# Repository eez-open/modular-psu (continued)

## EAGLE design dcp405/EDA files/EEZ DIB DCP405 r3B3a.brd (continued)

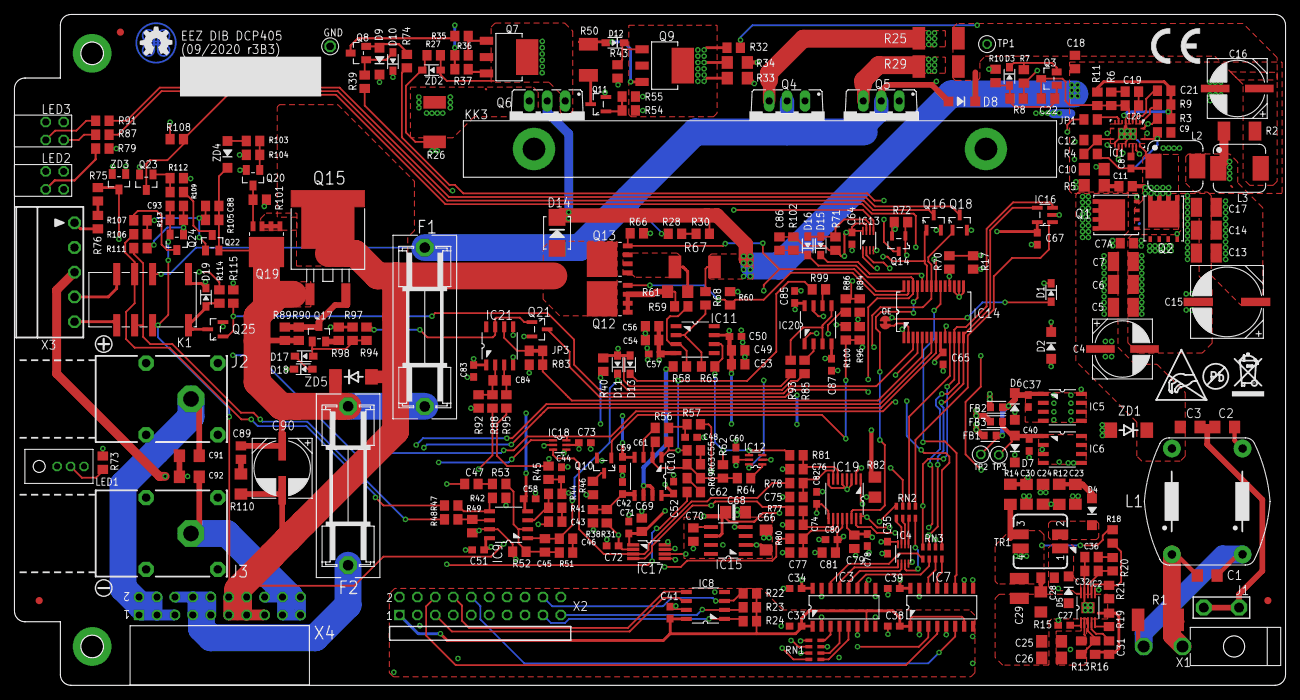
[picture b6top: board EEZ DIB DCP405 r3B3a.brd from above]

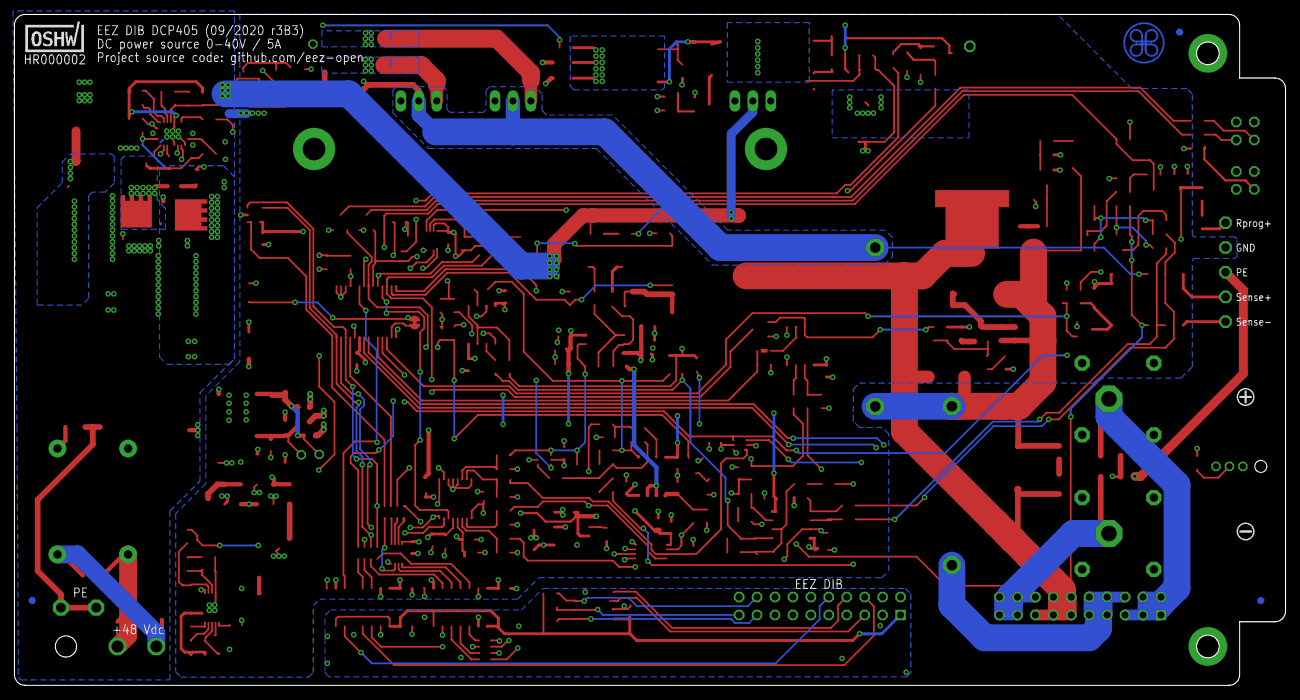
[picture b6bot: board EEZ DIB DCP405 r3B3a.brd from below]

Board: 4 copper layers, 180.0 x 95.0 mm, 322 parts (2 on the bottom side), 199 nets.

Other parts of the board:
EEZ_SIGNATURE: SIGNATURESMALL; SIGNATURE_5MM
U$1: RECYCLE_BIN1/8
U$2: CE_5MM
U$6: ESD_SYMBOL
U$7: PB_SMALL

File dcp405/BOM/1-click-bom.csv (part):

References,Qty,Description,Manufacturer,MPN,Manufacturer,MPN,Manufacturer,MPN,Manufacturer,MPN,Digikey,Mouser,RS,Newark,Farnell
"C1, C2, C3, C91, C92",5,10n/200V,,885342207005,,311-4491-1-ND,,CC1206KRX7RABB103,,VJ1206Y103KXCTW1BC,,,,,
"C10, C25, C26",3,2u2,,1276-2723-1-ND,,UMK316B7225KLHT,,CL31B225KBHNNNE,,,,,,,
C11,1,1n,,VJ0805A102JXACW1BC,,732-7858-1-ND,,GRM2195C1H102JA01D,,CL21C102JBCNNNC,,,,,
C12,1,15p,,MC0805N150J101CT,,1276-1163-1-ND,,C0805C150J5GACTU,,CL21C150JBANNNC,,,,,
"C13, C14, C17",3,10u,,GRT31CR61H106KE01L,,1276-6736-1-ND,,UMK316BBJ106KL-T,,CL31A106KBHNNNE,,,,,
C15,1,EEEFK1J101P,,EEEFK1J101P,,PCE3819CT-ND,,EEEFK1J101P,,EEEFK1J101P,,,,,
"C18, C53, C56, C69, C70, C79, C81",7,1u,,VJ0805Y105KXXTW1BC,,587-1283-1-ND,,C0805C105K4RACTU,,CL21B105KOFNNNE,,,,,
"C19, C21, C31, C36, C49, C54, C88, C93",8,10n,,VJ0805Y103JXXPW1BC,,490-7194-1-ND,,08055C103KAT2A,,CC0805KRX7R9103,,,,,
C20,1,150p,,0805N151J500CT,,1276-1828-1-ND,,C0805C151J5GACTU,,CC0805JRNPO9BN151,,,,,
C22,1,470p,,MC0805N471J500CT,,732-7837-1-ND,,0805CG471J9BB,,CC0805JRNPO9BN471,,,,,
"C23, C24, C30, C66",4,4u7,,C3216X7R1E475K160AC,,1276-2970-1-ND,,C1206C475K3RACTU,,GCM31CR71E475KA55L,,,,,
C28,1,330p,,C0805C331J5GACTU,,1276-1189-1-ND,,0805N331J500CT,,CL21C331JBANNNC,,,,,
C29,1,22u,,MC1210X226K250CT,,1276-3373-1-ND,,CL32A226KAJNNNE,,CL32A226KAJNNNE,,,,,
"C32, C45, C61",3,33p,,MC0805N330J500CT,,1276-1105-1-ND,,C0805C330J5GACTU,,CL21C330JBANNNC,,,,,
"C4, C16",2,EEEFK1H470P,,EEEFK1H470P,,PCE3815CT-ND,,EEEFK1H470P,,EEEFK1H470P,,,,,
"C43, C47",2,100p,,C0805C101JAGACTU,,399-15000-1-ND,,CC0805JRNP09BN101,,CL21C101JBANNNC,,,,,
"C5, C6, C7",3,4u7/100V,,CGA6M3X7S2A475K200AB,,587-5034-1-ND,,-,,,,,,,
"C55, C74, C75, C76, C77, C84, C86",7,4n7,,GRM2165C1H472JA01D,,732-12255-1-ND,,C2012C0G1H472J060AA,,GRM2165C1H472JA01D,,,,,
C62,1,6n8,,MC0805B682K500CT,,1276-1799-1-ND,,GRM2195C1H682JA01D,,CL21B682KBANNNC,,,,,
C68,1,4u7 tant.,,T491A475K006AT,,399-9717-1-ND,,T491A475K006AT,,T491A475K006AT,,,,,
"C7A, C9, C89",3,470n,,MC0805F474Z500CT,,1276-6482-1-ND,,0805CG471J9BB,,CL21B474KBFNNNE,,,,,
"C8, C27, C33, C34, C35, C37, C38, C39, C40, C41, C42, C44, C48, C50, C51, C52, C57, C58, C59, C60, C64, C65, C67, C71, C72, C73, C78, C80, C82, C83, C85, C87",32,100n,,C0603C104K4RAC7081,,490-4774-1-ND,,VJ0603Y104KXJAT,,CL10B104KA8NNNC,,,,,
C90,1,HHXC630A330MHA0,,-,,-,,,,,,,,,
"D1, D3, D10, D11, D12, D13, D15, D17, D18, D19",10,BAS316,,"BAS316,115",,1727-7370-1-ND,,"BAS316,115",,"BAS316,115",,,,,
D14,1,SK55,,SBRT5A50SA-13,,SK56A-LTPMSCT-ND,,SK56B R4,,SK55-DIO,,,,,
"D2, D4, D5",3,SKL16,,RB160MM-60TR,,RB160MM-60CT-ND,,RB160MM-60TR,,SKL16-DIO,,,,,
"D6, D7, D9",3,SKL14,,PMEG4010EGWX,,1727-7335-1-ND,,PMEG4010EGWX,,SKL14-DIO,,,,,
"F1, F2",2,ZH32,,-,,ZH32,,,,,,,,,
"FB1, FB2, FB3",3,BLM18AG102SH1D,,BLM18AG102SN1D,,490-7809-1-ND,,BLM18AG102SH1D,,BLM18AG102SH1D,,,,,
IC1,1,LM5145RGYT,,LM5145RGYT,,296-47121-1-ND,,-,,,,,,,
IC11,1,LTC2050HVCS8#PBF,,LTC2050HVCS8#PBF-ND,,LTC2050HVCS8#PBF,,-,,,,,,,
"IC12, IC18",2,SN74LVC1G3157DCKR,,SN74LVC1G3157DCKR,,296-14909-1-ND,,SN74LVC1G3157DCKR,,SN74LVC1G3157DCKR,,,,,
IC13,1,74AUP1G74DC.125,,"74AUP1G74DC,125",,1727-6029-1-ND,,"74AUP1G74DC,125",,74AUP1G74DC.125,,,,,
IC14,1,MCP23S17-E/SS,,MCP23S17-E/SS,,MCP23S17-E/SS-ND,,MCP23S17-E/SS,,MCP23S17-E/SS,,,,,
IC15,1,REF5025AIDR,,REF5025AIDG4,,296-39165-1-ND,,REF5025AID,,-,,,,,
IC16,1,TC77-5.0MCTTR,,TC77-5.0MCTTRCT-ND,,TC77-5.0MCTTR,,TC77-5.0MCTTR,,,,,,,
IC17,1,DAC8552IDGKR,,296-46082-1-ND,,-,,,,,,,,,
IC19,1,ADS1120IPWR,,296-37280-1-ND,,-,,,,,,,,,
IC2,1,TPS54060DGQ,,TPS54060DGQ .,,296-37148-1-ND,,TPS54060DGQ,,-,,,,,
IC20,1,LM293D,,LM293DT,,296-12848-1-ND,,LM293ADR,,LM293D-ST,,,,,
IC21,1,MAX9141ESA,,MAX9141ESA+,,MAX9141ESA+-ND,,MAX9141ESA+,,-,,,,,
"IC3, IC7",2,SI8641BB-B-IS1,,SI8641BB-B-IS1,,336-2566-ND,,Si8641BB-B-IS1,,-,,,,,
IC4,1,SN74LVC1G139DCUR,,SN74LVC1G139DCUR,,296-18203-1-ND,,-,,,,,,,
IC5,1,MC78L05,,MC78L05ABDR2G,,MC78L05ACDR2GOSCT-ND,,MC78L05ACDG,,MC78L05ACDG,,,,,
IC6,1,MC79L05,,MC79L05ACDR2G,,MC79L05ABDGOS-ND,,MC79L05ACDR2G,,MC79L05ACDG,,,,,
IC8,1,M24C32-WMN6P,,M24C32-WMN6P,,497-8644-1-ND,,M24C32-WMN6P,,M24C32-WMN6P,,,,,
"IC9, IC10",2,TL072D,,TL072CDT,,296-1282-1-ND,,TL072CD,,TL072CD-ST,,,,,
J1,1,4907,,36-4907-ND,,61-1537-11/0031,,,,,,,,,
J2,1,FCR7350R or BSM-420-R,,FCR7350R,,-,,SWEB 8094 Au / RT,,BSM-420-R,,,,,
J3,1,FCR7350B or BSM-420-B,,FCR7350B,,-,,SWEB 8094 Au / SW,,BSM-420-B,,,,,
K1,1,FTR-C1GA005G-B05,,-,,FTR-C1GA005G,,FTR-C1GA005G-B05,,,,,,,
L1,1,RN112-4-02-0M7,,817-2100-ND,,-,,,,,,,,,
L2,1,ETQ-P4M100KFM,,ETQP4M100KFM,,P124167CT-ND,,,,,,,,,
L3,1,HPI0630-3R3,,IHLP2020CZER3R3M11,,445-180834-1-ND,,HPI0630-3R3,,,,,,,
LED1,1,WP42WUM/EGW,,754-1718-ND,,L-42WUM/1EGWT,,,,,,,,,
LED2,1,WP934MD/2LID,,754-2000-ND,,-,,,,,,,,,
LED3,1,WP934MD/LYLID,,754-2008-ND,,-,,,,,,,,,
Q1,1,BSC117N08NS5ATMA1,,BSC117N08NS5ATMA1,,BSC117N08NS5ATMA1CT-ND,,BSC117N08NS5ATMA1,,,,,,,
"Q10, Q16, Q18, Q21, Q25",5,2N7002,,2N7002K-7,,T2N7002AKLMCT-ND,,2N7002,,2N7002LT1G,,,,,
Q11,1,BSS205NH6327XTSA1,,BSS205NH6327XTSA1,,BSS205NH6327XTSA1CT-ND,,BSS205NH6327XTSA1,,BSS205NH6327XTSA1,,,,,
"Q12, Q13",2,PSMN0R9-25YLC,,"PSMN0R9-25YLC,115",,1727-5292-1-ND,,"PSMN0R9-25YLC,115",,PSMN0R9-25YLC.115,,,,,
Q14,1,BSS84P,,BSS84PH6327XTSA2,,BSS84PH6433XTMA1CT-ND,,BSS84P,,,,,,,
Q15,1,BT139B-600E,,"BT139B-600,118",,1740-1053-1-ND,,"BT139B-600,118",,BT139B-600E.118,,,,,
Q17,1,FMMT493TA,,FMMT493ATA,,FMMT493CT-ND,,FMMT493TA,,FMMT493TA,,,,,
Q19,1,PSMN013-60YL,,PSMN013-60YLX,,1727-2589-1-ND,,-,,,,,,,
Q2,1,BSC039N06NSATMA1,,BSC039N06NSATMA1,,BSC039N06NSATMA1CT-ND,,BSC039N06NSATMA1,,BSC039N06NS,,,,,
"Q20, Q23, Q24",3,MMBT5551,,MMBT5551LT1G,,MMBT5551LT1GOSCT-ND,,MMBT5551LT1G,,MMBT5551,,,,,
"Q3, Q8, Q22",3,MMBT5401,,MMBT5401LT3G,,MMBT5401-FDICT-ND,,MMBT5401,,MMBT5401,,,,,
"Q4, Q5",2,D45H11FP,,497-12486-5-ND,,-,,,,,,,,,
Q6,1,FQPF11P06,,FQPF11P06FS-ND,,FQPF11P06,,-,,,,,,,
Q7,1,BCP56,,BCP56TX,,BCP5616QTADICT-ND,,BCP56-16T3G,,BCP56-16T1G,,,,,
Q9,1,NZT605,,NZT605,,NZT605CT-ND,,NZT605,,NZT605,,,,,
R10,1,11K,,MCWR08X1102FTL,,A126334CT-ND,,CRCW080511K0FKEA,,0805S8F1102T5E,,,,,
"R106, R111",2,750R,,MCWR08X7500FTL,,A126385CT-ND,,RN73C2A750RB,,0805S8F7500T5E,,,,,
R107,1,3K3,,MCWR08X3301FTL,,A129755CT-ND,,CRG0805F3K3,,0805S8F3301T5E,,,,,
R11,1,3K9,,MCWR08X3901FTL,,A126369CT-ND,,CRCW08053K90FKEA,,SMD0805-3K9-1%,,,,,
"R16, R32, R40, R45, R56, R57, R74, R77, R78, R80, R81",11,2K2,,RC0805FR-072K2L,,311-2.20KCRCT-ND,,CRCW08052K20FKEA,,0805S8F2201T5E,,,,,
"R18, R20",2,86K6,,ERJ6ENF8662V,,311-86.6KCRCT-ND,,CRCW080586K6FKTABC,,,,,,,
R19,1,330K,,MCWR08X3303FTL,,A126361CT-ND,,CRCW0805330KFKEA,,0805S8F3303T5E,,,,,
"R2, R50",2,15R/0.75W,,CRGCQ2010J15R,,A129910CT-ND,,RK73HW2HTTE15R0F,,201007J0150T4E,,,,,
"R21, R63",2,8K2,,MCWR08X8201FTL,,311-8.20KCRCT-ND,,CRG0805F8K2,,0805S8J0822T5E,,,,,
"R25, R29",2,0R1/2-3W,,MCLRP12JTWSR100,,696-1680-1-ND,,CRA2512-FZ-R100ELF,,LRP12FTDRR100,,,,,
R26,1,2R2/2-3W,,35202R2JT,,CRM2512-JW-2R2ELFCT-ND,,35222R2JT,,WF25P2R2JTL,,,,,
"R27, R28, R30, R35, R84, R86, R96, R100, R102",9,4K7,,CRGCQ0805F4K7,,311-4.70KCRCT-ND,,CRG0805F4K7,,0805S8F4701T5E,,,,,
"R3, R6, R7, R17, R22, R23, R24, R31, R41, R44, R52, R53, R71, R83, R85, R92, R93, R95, R99, R108, R109",21,10K,,RC0805FR-0710KL,,311-10.0KCRCT-ND,,CRG0805F10K,,RC0805FR-0710K,,,,,
"R36, R43, R69, R70, R89, R90, R94, R101",8,1K,,WCR0805-1K0FI,,RC0805FR-071KL,,CRG0805F1K0,,RC0805FR-071K,,,,,
"R37, R38, R54",3,220R,,WCR0805-220RFI,,RMCF0805FT220RCT-ND,,CRG0805F220R,,0805S8F2200T5E,,,,,
"R39, R46, R62, R103, R104",5,22K,,MCWR08X2202FTL,,RMCF0805FT22K0CT-ND,,CRCW080522K0FKEA,,0805S8J0223T5E,,,,,
"R4, R64, R75, R76, R79, R114",6,470R,,WCR0805-470RFI,,311-470CRCT-ND,,CRG0805F470R,,RC0805FR-07470R,,,,,
"R42, R49",2,7K5 0.1%,,MCTC0525B7501T5E,,YAG1974CT-ND,,AR05BTCW7501,,,,,,,
"R47, R48",2,124K 0.1%,,WF08U1243BTL,,P124KDACT-ND,,CPF0805B124KE1,,ERA6AEB1243V,,,,,
"R5, R12, R14, R15, R33, R34, R82",7,10R,,RC1206FR-0710RL,,311-10.0CRCT-ND,,CR1206-FX-10R0ELF,,1206S4J0100T5E,,,,,
"R58, R65",2,39K 0.1%,,MCWF08R3902BTL,,P20774CT-ND,,CPF-A-0805B39KE1,,AR05BTCW3902,,,,,
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
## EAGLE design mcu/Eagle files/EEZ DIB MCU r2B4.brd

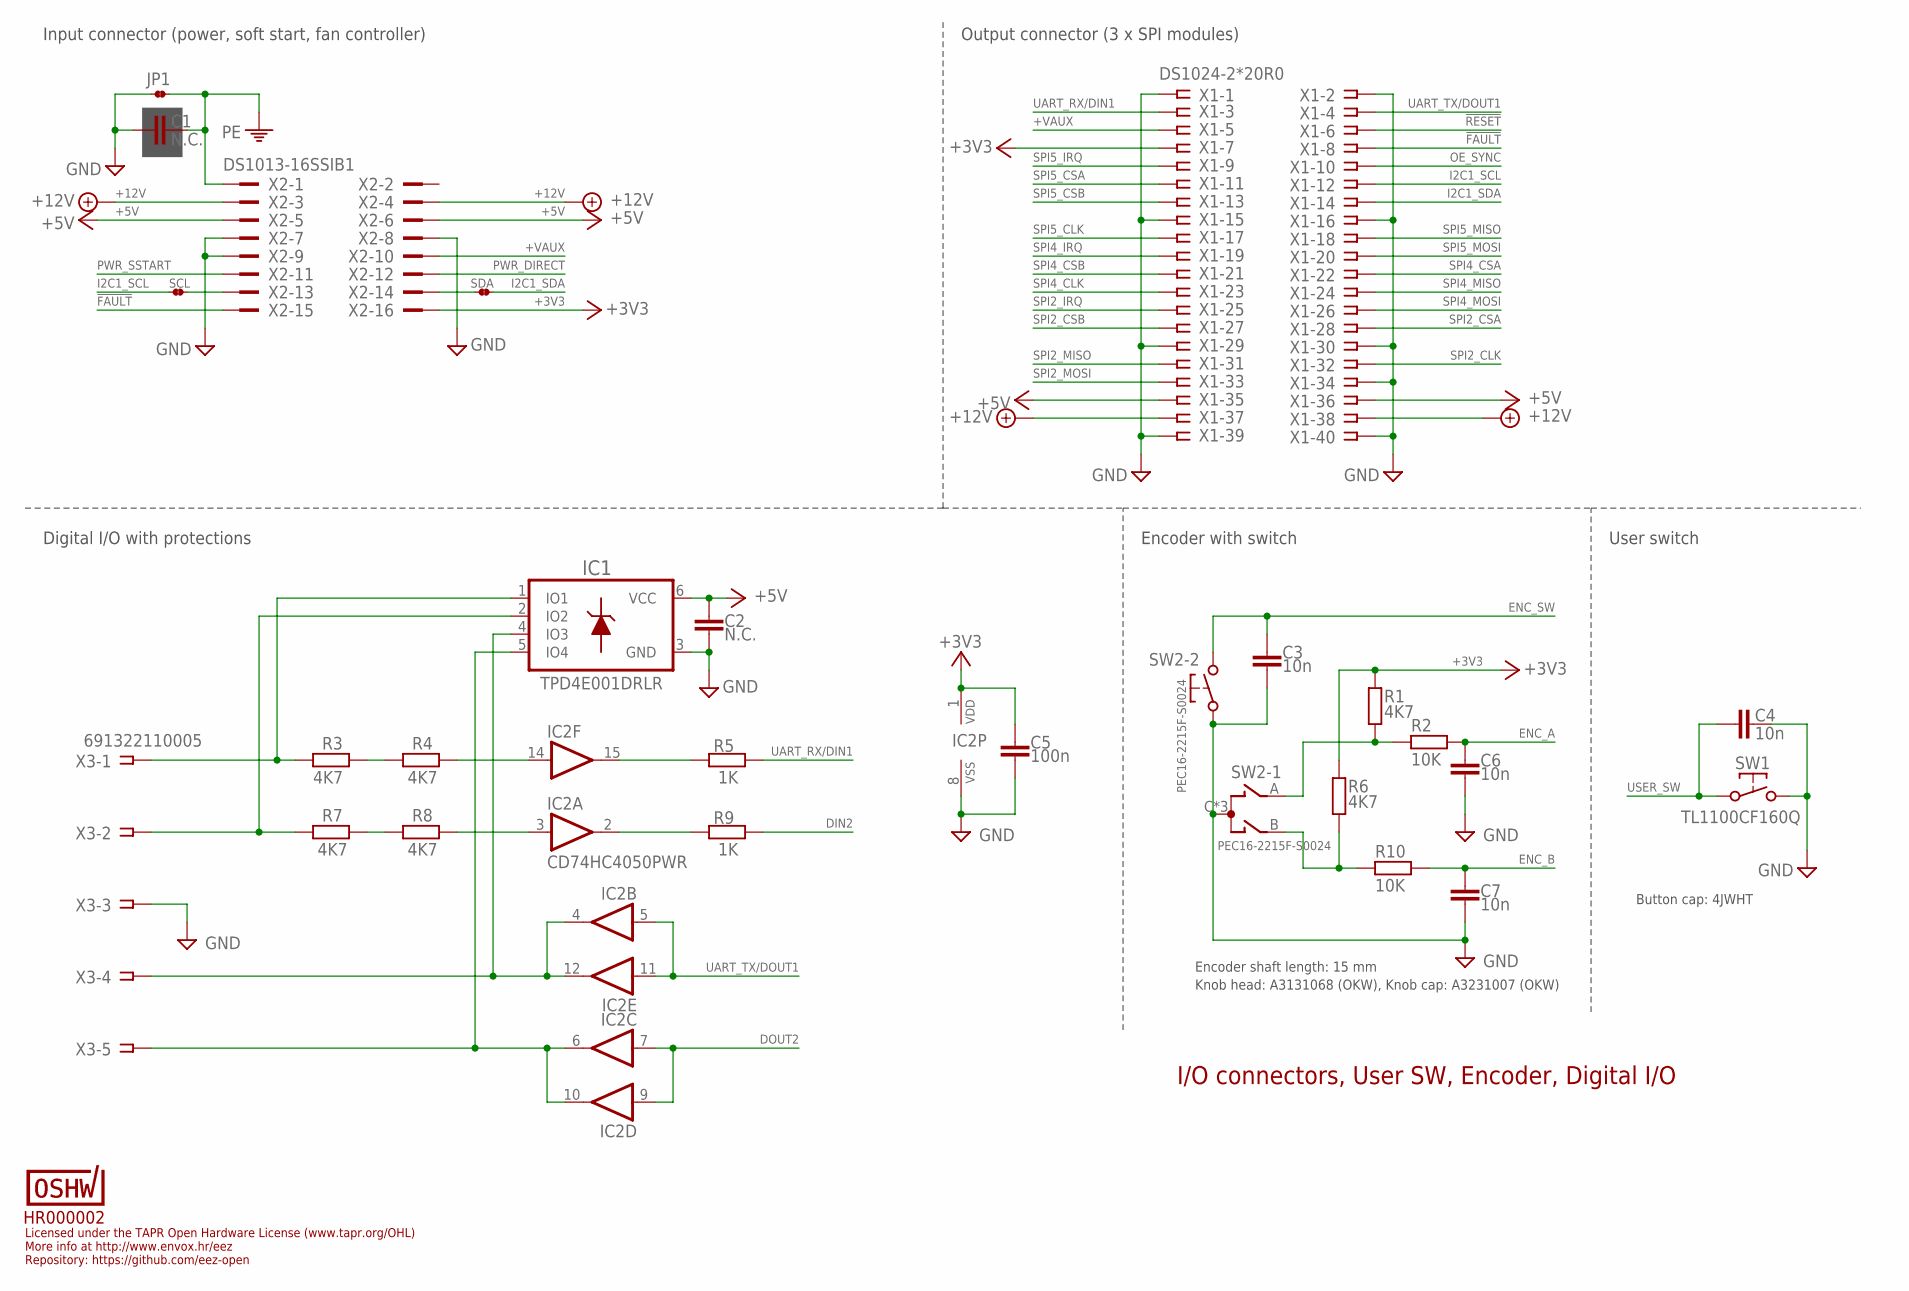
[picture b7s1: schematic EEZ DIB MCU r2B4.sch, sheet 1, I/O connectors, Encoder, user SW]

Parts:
C1: N.C.; C0805
C2: N.C.; C0603
C3, C4, C6, C7: 10n; C0805
C5: 100n; C0603
IC1: TPD4E001DRLR; DRL6
IC2: CD74HC4050PWR; PW16
JP1: JP2-NOCUT
R1, R3, R4, R6, R7, R8: 4K7; R0805
R2, R10: 10K; R0805
R5, R9: 1K; R0805
SCL: JP2-NOCUT
SDA: JP2-NOCUT
SW1: TL1100CF160Q; TL1100C
SW2: PEC16-2215F-S0024; PEC16-2215F
U$3: HR000002; CERT-SMALL-SILK
X1: DS1024-2*20R0; ZL263-40DG
X2: DS1013-16SSIB1; IDC-16PIN
X3: 691322110005; MC1,5/5-G-3,5

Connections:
!FAULT: X1.8, X2.15; also elsewhere on the board
!RESET: X1.6; also elsewhere on the board
+3V3: C5.1, IC2.1 (VDD), R1.1, R6.1, X1.7, X2.16; also elsewhere on the board
+5V: C2.1, IC1.6 (VCC), X1.35, X1.36, X2.5, X2.6; also elsewhere on the board
+12V: X1.37, X1.38, X2.3, X2.4
+VAUX: X1.5, X2.10; also elsewhere on the board
DIN2: R9.2; also elsewhere on the board
DOUT2: IC2.7 (I), IC2.9 (I); also elsewhere on the board
ENC_A: C6.2, R2.1; also elsewhere on the board
ENC_B: C7.1, R10.1; also elsewhere on the board
ENC_SW: C3.2, SW2.E (2); also elsewhere on the board
EOUT_A: R6.2, R10.2, SW2.B
EOUT_B: R1.2, R2.2, SW2.A
GND: C1.2, C2.2, C3.1, C4.1, C5.2, C6.1, C7.2, IC1.3 (GND), IC2.8 (VSS), JP1.1, SW1.2, SW2.C, SW2.D (1), SW2.GND1 (C), SW2.GND2 (C), X1.1, X1.2, X1.15, X1.16, X1.29, X1.30, X1.34, X1.39, X1.40, X2.7, X2.8, X2.9, X3.3; also elsewhere on the board
I2C1_SCL: SCL.1, X1.12; also elsewhere on the board
I2C1_SDA: SDA.2, X1.14; also elsewhere on the board
unnamed: IC1.1 (IO1), R3.1, X3.1
unnamed: SCL.2, X2.13
unnamed: SDA.1, X2.14
unnamed: IC1.2 (IO2), R7.1, X3.2
unnamed: R7.2, R8.1
unnamed: R3.2, R4.1
unnamed: IC2.15 (O), R5.1
unnamed: IC2.2 (O), R9.1
unnamed: IC2.14 (I), R4.2
unnamed: IC2.3 (I), R8.2
unnamed: IC1.4 (IO3), IC2.4 (O), IC2.12 (O), X3.4
unnamed: IC1.5 (IO4), IC2.6 (O), IC2.10 (O), X3.5
OE_SYNC: X1.10; also elsewhere on the board
PE: C1.1, JP1.2, X2.1; also elsewhere on the board
PWR_DIRECT: X2.12; also elsewhere on the board
PWR_SSTART: X2.11; also elsewhere on the board
SPI2_CLK: X1.32; also elsewhere on the board
SPI2_CSA: X1.28; also elsewhere on the board
SPI2_CSB: X1.27; also elsewhere on the board
SPI2_IRQ: X1.25; also elsewhere on the board
SPI2_MISO: X1.31; also elsewhere on the board
SPI2_MOSI: X1.33; also elsewhere on the board
SPI4_CLK: X1.23; also elsewhere on the board
SPI4_CSA: X1.22; also elsewhere on the board
SPI4_CSB: X1.21; also elsewhere on the board
SPI4_IRQ: X1.19; also elsewhere on the board
SPI4_MISO: X1.24; also elsewhere on the board
SPI4_MOSI: X1.26; also elsewhere on the board
SPI5_CLK: X1.17; also elsewhere on the board
SPI5_CSA: X1.11; also elsewhere on the board
SPI5_CSB: X1.13; also elsewhere on the board
SPI5_IRQ: X1.9; also elsewhere on the board
SPI5_MISO: X1.18; also elsewhere on the board
SPI5_MOSI: X1.20; also elsewhere on the board
UART_RX/DIN1: R5.2, X1.3; also elsewhere on the board
UART_TX/DOUT1: IC2.5 (I), IC2.11 (I), X1.4; also elsewhere on the board
USER_SW: C4.2, SW1.1; also elsewhere on the board

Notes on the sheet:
Licensed under the TAPR Open Hardware License (www.tapr.org/OHL)
Repository: https://github.com/eez-open
More info at http://www.envox.hr/eez
Encoder shaft length: 15 mm
Knob head: A3131068 (OKW), Knob cap: A3231007 (OKW)
I/O connectors, User SW, Encoder, Digital I/O
Digital I/O with protections
Encoder with switch
User switch
Input connector (power, soft start, fan controller)
Output connector (3 x SPI modules)
Button cap: 4JWHT

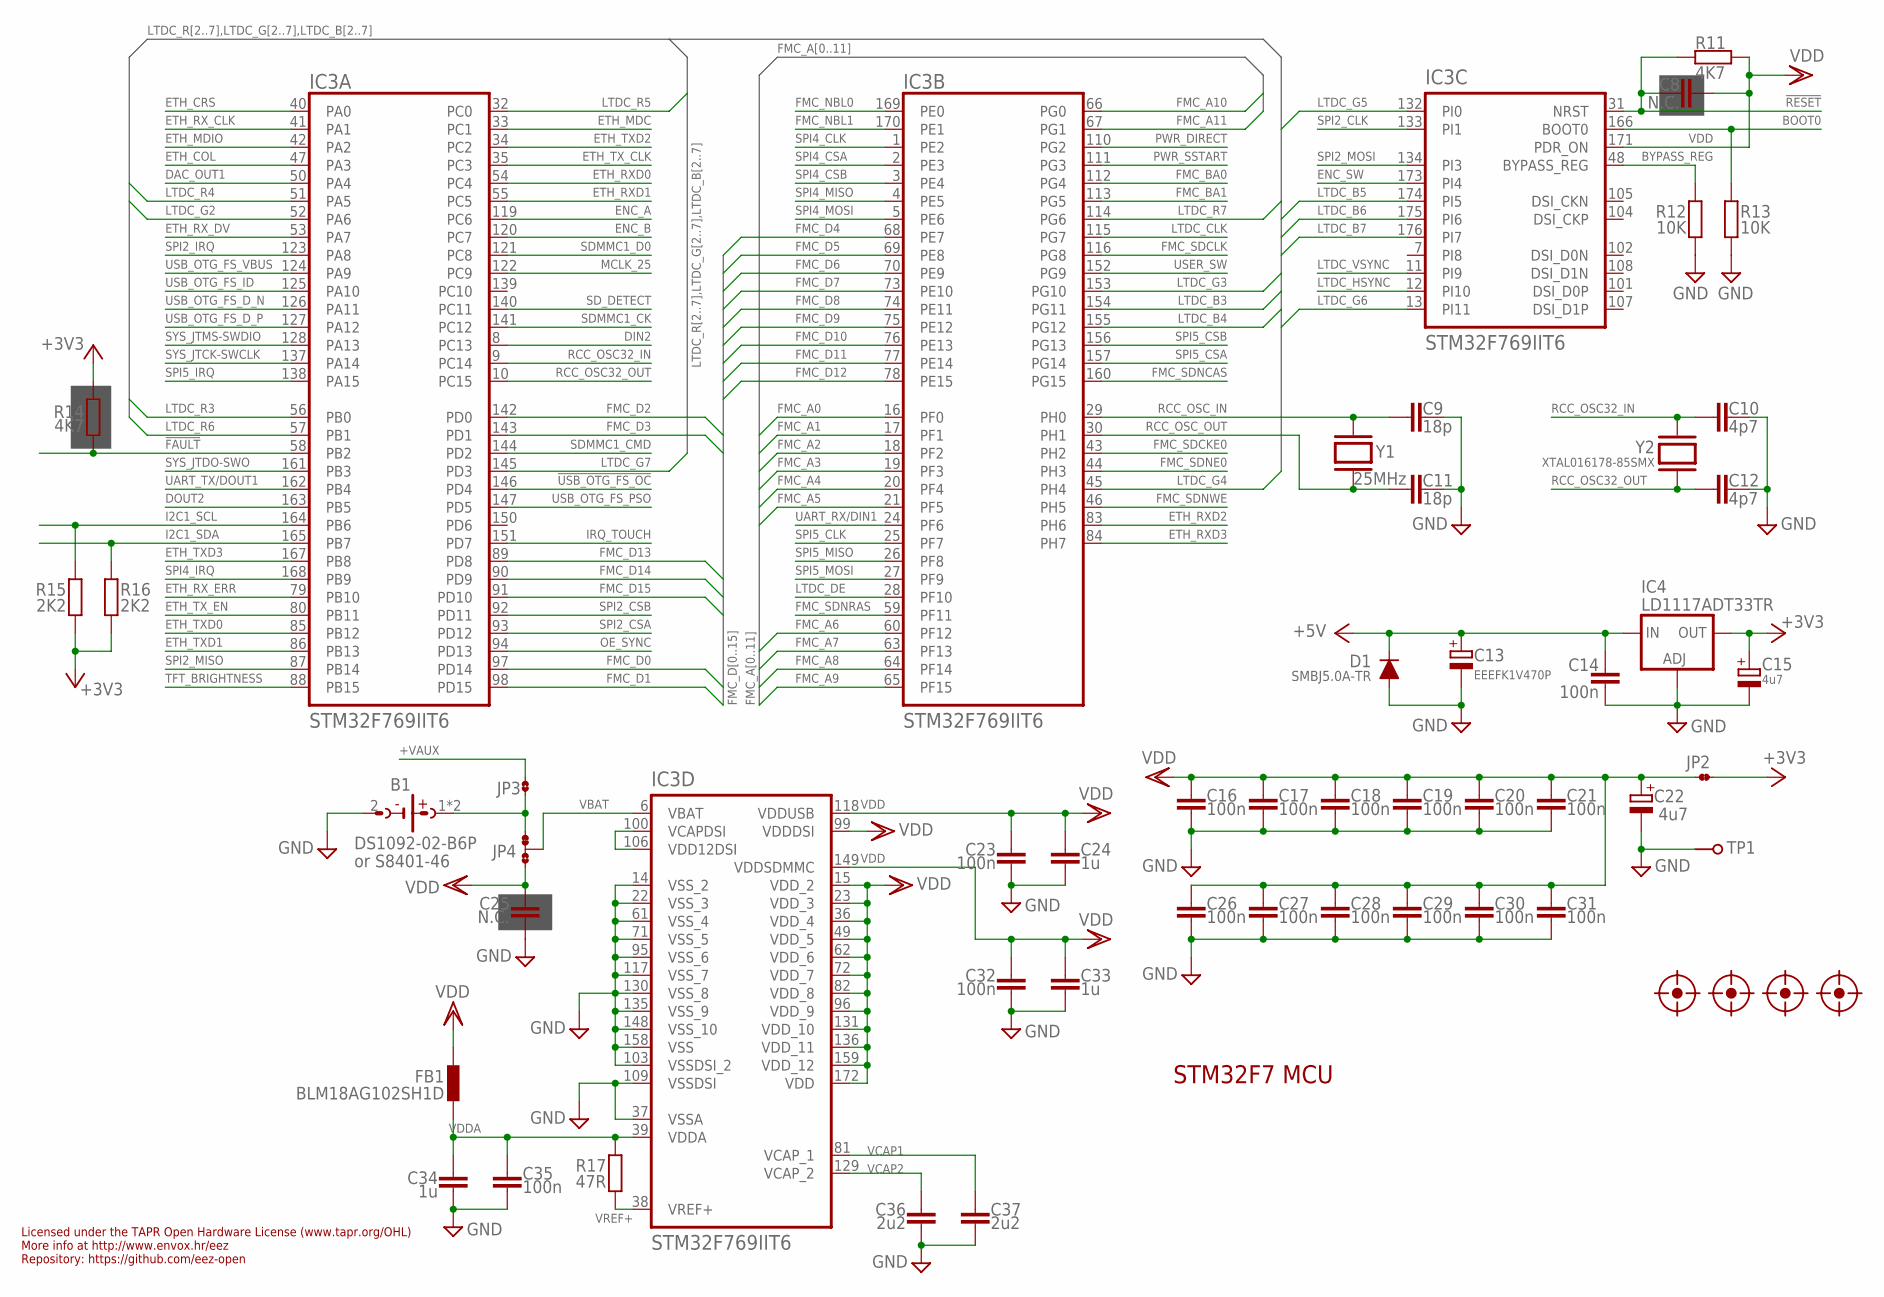
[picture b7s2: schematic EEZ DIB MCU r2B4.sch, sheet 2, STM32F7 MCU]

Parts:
B1: DS1092-02-B6P; S8401-46
C8: N.C.; C0805
C9, C11: 18p; C0603
C10, C12: 4p7; C0603
C13: EEEFK1V470P; CAPAE660X610N
C14, C16, C17, C18, C19, C20, C21, C23, C26, C27, C28, C29, C30, C31, C32, C35: 100n; C0603
C15, C22: 4u7; EC1206
C24, C33, C34: 1u; C0805
C25: N.C.; C0603
C36, C37: 2u2; C0805
D1: SMBJ5.0A-TR; DO214AA
FB1: BLM18AG102SH1D; BEAD0603
FM1, FM2, FM3, FM4: FIDUCIAL
IC3: STM32F769IIT6; LQFP-176_24X24MM
IC4: LD1117ADT33TR; DPACK
JP2: JP2-NOCUT
JP3: JP2-CUT
JP4: JP3-CUT
R11, R14: 4K7; R0805
R12, R13: 10K; R0805
R15, R16: 2K2; R0805
R17: 47R; R0805
TP1: PCB_TEST_TABSHIELD; PCB_SHIELD_TAB
Y1: 25MHz; HC-49/4H
Y2: XTAL016178-85SMX; 85SMX

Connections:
!FAULT: IC3.58 (PB2), R14.2; also elsewhere on the board
!RESET: C8.1, IC3.31 (NRST), R11.2; also elsewhere on the board
!USB_OTG_FS_OC: IC3.146 (PD4); also elsewhere on the board
+3V3: C15.+, IC4.4 (OUT), JP2.2, R14.1, R15.1, R16.1; also elsewhere on the board
+5V: C13.1 (+), C14.1, D1.C, IC4.3 (IN); also elsewhere on the board
+VAUX: JP3.2; also elsewhere on the board
BOOT0: IC3.166 (BOOT0), R13.2; also elsewhere on the board
BYPASS_REG: IC3.48 (BYPASS_REG), R12.2
DAC_OUT1: IC3.50 (PA4); also elsewhere on the board
DIN2: IC3.8 (PC13); also elsewhere on the board
DOUT2: IC3.163 (PB5); also elsewhere on the board
ENC_A: IC3.119 (PC6); also elsewhere on the board
ENC_B: IC3.120 (PC7); also elsewhere on the board
ENC_SW: IC3.173 (PI4); also elsewhere on the board
ETH_COL: IC3.47 (PA3); also elsewhere on the board
ETH_CRS: IC3.40 (PA0); also elsewhere on the board
ETH_MDC: IC3.33 (PC1); also elsewhere on the board
ETH_MDIO: IC3.42 (PA2); also elsewhere on the board
ETH_RXD0: IC3.54 (PC4); also elsewhere on the board
ETH_RXD1: IC3.55 (PC5); also elsewhere on the board
ETH_RXD2: IC3.83 (PH6); also elsewhere on the board
ETH_RXD3: IC3.84 (PH7); also elsewhere on the board
ETH_RX_CLK: IC3.41 (PA1); also elsewhere on the board
ETH_RX_DV: IC3.53 (PA7); also elsewhere on the board
ETH_RX_ERR: IC3.79 (PB10); also elsewhere on the board
ETH_TXD0: IC3.85 (PB12); also elsewhere on the board
ETH_TXD1: IC3.86 (PB13); also elsewhere on the board
ETH_TXD2: IC3.34 (PC2); also elsewhere on the board
ETH_TXD3: IC3.167 (PB8); also elsewhere on the board
ETH_TX_CLK: IC3.35 (PC3); also elsewhere on the board
ETH_TX_EN: IC3.80 (PB11); also elsewhere on the board
FMC_A0: IC3.16 (PF0); also elsewhere on the board
FMC_A1: IC3.17 (PF1); also elsewhere on the board
FMC_A2: IC3.18 (PF2); also elsewhere on the board
FMC_A3: IC3.19 (PF3); also elsewhere on the board
FMC_A4: IC3.20 (PF4); also elsewhere on the board
FMC_A5: IC3.21 (PF5); also elsewhere on the board
FMC_A6: IC3.60 (PF12); also elsewhere on the board
FMC_A7: IC3.63 (PF13); also elsewhere on the board
FMC_A8: IC3.64 (PF14); also elsewhere on the board
FMC_A9: IC3.65 (PF15); also elsewhere on the board
FMC_A10: IC3.66 (PG0); also elsewhere on the board
FMC_A11: IC3.67 (PG1); also elsewhere on the board
FMC_BA0: IC3.112 (PG4); also elsewhere on the board
FMC_BA1: IC3.113 (PG5); also elsewhere on the board
FMC_D0: IC3.97 (PD14); also elsewhere on the board
FMC_D1: IC3.98 (PD15); also elsewhere on the board
FMC_D2: IC3.142 (PD0); also elsewhere on the board
FMC_D3: IC3.143 (PD1); also elsewhere on the board
FMC_D4: IC3.68 (PE7); also elsewhere on the board
FMC_D5: IC3.69 (PE8); also elsewhere on the board
FMC_D6: IC3.70 (PE9); also elsewhere on the board
FMC_D7: IC3.73 (PE10); also elsewhere on the board
FMC_D8: IC3.74 (PE11); also elsewhere on the board
FMC_D9: IC3.75 (PE12); also elsewhere on the board
FMC_D10: IC3.76 (PE13); also elsewhere on the board
FMC_D11: IC3.77 (PE14); also elsewhere on the board
FMC_D12: IC3.78 (PE15); also elsewhere on the board
FMC_D13: IC3.89 (PD8); also elsewhere on the board
FMC_D14: IC3.90 (PD9); also elsewhere on the board
FMC_D15: IC3.91 (PD10); also elsewhere on the board
FMC_NBL0: IC3.169 (PE0); also elsewhere on the board
FMC_NBL1: IC3.170 (PE1); also elsewhere on the board
FMC_SDCKE0: IC3.43 (PH2); also elsewhere on the board
FMC_SDCLK: IC3.116 (PG8); also elsewhere on the board
FMC_SDNCAS: IC3.160 (PG15); also elsewhere on the board
FMC_SDNE0: IC3.44 (PH3); also elsewhere on the board
FMC_SDNRAS: IC3.59 (PF11); also elsewhere on the board
FMC_SDNWE: IC3.46 (PH5); also elsewhere on the board
GND: B1.2 (-), C9.1, C10.2, C11.1, C12.2, C13.2 (-), C14.2, C15.-, C16.2, C17.2, C18.2, C19.2, C20.2, C21.2, C22.-, C23.2, C24.2, C25.2, C26.2, C27.2, C28.2, C29.2, C30.2, C31.2, C32.2, C33.2, C34.2, C35.2, C36.2, C37.2, D1.A, IC3.14 (VSS_2), IC3.22 (VSS_3), IC3.37 (VSSA), IC3.61 (VSS_4), IC3.71 (VSS_5), IC3.95 (VSS_6), IC3.103 (VSSDSI_2), IC3.109 (VSSDSI), IC3.117 (VSS_7), IC3.130 (VSS_8), IC3.135 (VSS_9), IC3.148 (VSS_10), IC3.158 (VSS), IC4.1 (ADJ), R12.1, R13.1, TP1.1; also elsewhere on the board
I2C1_SCL: IC3.164 (PB6), R15.2; also elsewhere on the board
I2C1_SDA: IC3.165 (PB7), R16.2; also elsewhere on the board
IRQ_TOUCH: IC3.151 (PD7); also elsewhere on the board
LTDC_B3: IC3.154 (PG11); also elsewhere on the board
LTDC_B4: IC3.155 (PG12); also elsewhere on the board
LTDC_B5: IC3.174 (PI5); also elsewhere on the board
LTDC_B6: IC3.175 (PI6); also elsewhere on the board
LTDC_B7: IC3.176 (PI7); also elsewhere on the board
LTDC_CLK: IC3.115 (PG7); also elsewhere on the board
LTDC_DE: IC3.28 (PF10); also elsewhere on the board
LTDC_G2: IC3.52 (PA6); also elsewhere on the board
LTDC_G3: IC3.153 (PG10); also elsewhere on the board
LTDC_G4: IC3.45 (PH4); also elsewhere on the board
LTDC_G5: IC3.132 (PI0); also elsewhere on the board
LTDC_G6: IC3.13 (PI11); also elsewhere on the board
LTDC_G7: IC3.145 (PD3); also elsewhere on the board
LTDC_HSYNC: IC3.12 (PI10); also elsewhere on the board
LTDC_R3: IC3.56 (PB0); also elsewhere on the board
LTDC_R4: IC3.51 (PA5); also elsewhere on the board
LTDC_R5: IC3.32 (PC0); also elsewhere on the board
LTDC_R6: IC3.57 (PB1); also elsewhere on the board
LTDC_R7: IC3.114 (PG6); also elsewhere on the board
LTDC_VSYNC: IC3.11 (PI9); also elsewhere on the board
MCLK_25: IC3.122 (PC9); also elsewhere on the board
unnamed: B1.1 (+), B1.3 (+), JP3.1, JP4.NC
unnamed: IC3.100 (VCAPDSI), IC3.106 (VDD12DSI)
OE_SYNC: IC3.94 (PD13); also elsewhere on the board
PWR_DIRECT: IC3.110 (PG2); also elsewhere on the board
PWR_SSTART: IC3.111 (PG3); also elsewhere on the board
RCC_OSC32_IN: C10.1, IC3.9 (PC14), Y2.1
RCC_OSC32_OUT: C12.1, IC3.10 (PC15), Y2.4 (2)
RCC_OSC_IN: C9.2, IC3.29 (PH0), Y1.2
RCC_OSC_OUT: C11.2, IC3.30 (PH1), Y1.1
SDMMC1_CK: IC3.141 (PC12); also elsewhere on the board
SDMMC1_CMD: IC3.144 (PD2); also elsewhere on the board
SDMMC1_D0: IC3.121 (PC8); also elsewhere on the board
SD_DETECT: IC3.140 (PC11); also elsewhere on the board
SPI2_CLK: IC3.133 (PI1); also elsewhere on the board
SPI2_CSA: IC3.93 (PD12); also elsewhere on the board
SPI2_CSB: IC3.92 (PD11); also elsewhere on the board
SPI2_IRQ: IC3.123 (PA8); also elsewhere on the board
SPI2_MISO: IC3.87 (PB14); also elsewhere on the board
SPI2_MOSI: IC3.134 (PI3); also elsewhere on the board
SPI4_CLK: IC3.1 (PE2); also elsewhere on the board
SPI4_CSA: IC3.2 (PE3); also elsewhere on the board
SPI4_CSB: IC3.3 (PE4); also elsewhere on the board
SPI4_IRQ: IC3.168 (PB9); also elsewhere on the board
SPI4_MISO: IC3.4 (PE5); also elsewhere on the board
SPI4_MOSI: IC3.5 (PE6); also elsewhere on the board
SPI5_CLK: IC3.25 (PF7); also elsewhere on the board
SPI5_CSA: IC3.157 (PG14); also elsewhere on the board
SPI5_CSB: IC3.156 (PG13); also elsewhere on the board
SPI5_IRQ: IC3.138 (PA15); also elsewhere on the board
SPI5_MISO: IC3.26 (PF8); also elsewhere on the board
SPI5_MOSI: IC3.27 (PF9); also elsewhere on the board
SYS_JTCK-SWCLK: IC3.137 (PA14); also elsewhere on the board
SYS_JTDO-SWO: IC3.161 (PB3); also elsewhere on the board
SYS_JTMS-SWDIO: IC3.128 (PA13); also elsewhere on the board
TFT_BRIGHTNESS: IC3.88 (PB15); also elsewhere on the board
UART_RX/DIN1: IC3.24 (PF6); also elsewhere on the board
UART_TX/DOUT1: IC3.162 (PB4); also elsewhere on the board
USB_OTG_FS_D_N: IC3.126 (PA11); also elsewhere on the board
USB_OTG_FS_D_P: IC3.127 (PA12); also elsewhere on the board
USB_OTG_FS_ID: IC3.125 (PA10); also elsewhere on the board
USB_OTG_FS_PSO: IC3.147 (PD5); also elsewhere on the board
USB_OTG_FS_VBUS: IC3.124 (PA9); also elsewhere on the board
USER_SW: IC3.152 (PG9); also elsewhere on the board
VBAT: IC3.6 (VBAT), JP4.COM
VCAP1: C37.1, IC3.81 (VCAP_1)
VCAP2: C36.1, IC3.129 (VCAP_2)
VDD: C8.2, C16.1, C17.1, C18.1, C19.1, C20.1, C21.1, C22.+, C23.1, C24.1, C25.1, C26.1, C27.1, C28.1, C29.1, C30.1, C31.1, C32.1, C33.1, FB1.P$1 (1), IC3.15 (VDD_2), IC3.23 (VDD_3), IC3.36 (VDD_4), IC3.49 (VDD_5), IC3.62 (VDD_6), IC3.72 (VDD_7), IC3.82 (VDD_8), IC3.96 (VDD_9), IC3.99 (VDDDSI), IC3.118 (VDDUSB), IC3.131 (VDD_10), IC3.136 (VDD_11), IC3.149 (VDDSDMMC), IC3.159 (VDD_12), IC3.171 (PDR_ON), IC3.172 (VDD), JP2.1, JP4.NO, R11.1
VDDA: C34.1, C35.1, FB1.P$2 (2), IC3.39 (VDDA), R17.2
VREF+: IC3.38 (VREF+), R17.1

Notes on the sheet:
Licensed under the TAPR Open Hardware License (www.tapr.org/OHL)
Repository: https://github.com/eez-open
More info at http://www.envox.hr/eez
STM32F7 MCU
or S8401-46
